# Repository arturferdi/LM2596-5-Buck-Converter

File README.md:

# LM2596-5 Fixed 5V Buck Converter

A compact step-down (buck) switching regulator based on the **Texas Instruments LM2596-5.0**, delivering a regulated **5V / 3A** output from an unregulated DC input up to 40V. Designed for embedded systems, IoT field devices, and general-purpose power supply applications.

---

## Table of Contents

- [Overview](#overview)
- [Schematic](#schematic)
- [PCB Design](#pcb-design)
- [Board Dimensions](#board-dimensions)
- [Bill of Materials (BOM)](#bill-of-materials-bom)
- [IC Electrical Characteristics](#ic-electrical-characteristics)
- [Application Design Notes](#application-design-notes)
  - [Input Capacitor (C_IN)](#input-capacitor-cin)
  - [Output Capacitor (C_OUT)](#output-capacitor-cout)
  - [Catch Diode (D1)](#catch-diode-d1)
  - [Inductor Selection](#inductor-selection)

---

## Overview

This module implements a **non-synchronous step-down DC-DC converter** using the LM2596-5.0 fixed-output variant. The LM2596 integrates all active functions for a buck regulator — including a fixed 150 kHz oscillator, internal error amplifier, and cycle-by-cycle current limiting — requiring only four external passive components.

| Parameter | Value |
|---|---|
| Topology | Non-synchronous Buck (Step-Down) |
| IC | LM2596-5.0 (TI) |
| Fixed Output Voltage | 5.0 V |
| Maximum Output Current | 3 A |
| Input Voltage Range | 7 V – 40 V |
| Switching Frequency | 150 kHz (fixed) |
| Output Voltage Accuracy | ±4% over line and load |
| Package | TO-220 (NDH) / TO-263 (KTT) |
| Thermal Protection | Yes (internal thermal shutdown) |
| Current Limit | Yes (two-stage frequency foldback) |
| Shutdown / Enable | Active-low via ON/OFF pin |

---

## Schematic

Also you can download the pdf schematic from `\PDF_Schematic`

The schematic follows the standard fixed-output buck topology per the LM2596 datasheet Figure 9-10:

---

## PCB Design

**Design rules and layout notes:**

- High-current paths (VIN → IC → L1 → VOUT and D1 freewheeling loop) use **wide copper pours** and are kept as short as possible to minimize parasitic inductance.
- The **output switch pin (Pin 1)** copper area is minimized to reduce EMI radiation from the switching node.
- C_IN and C_OUT are placed as close as possible to the IC with short return paths to GND.
- D1 (catch diode) is placed directly between Pin 2 (OUTPUT) and GND, adjacent to the IC.
- Feedback trace (Pin 4) is routed away from the inductor to prevent flux-induced noise coupling.
- **Ground plane** construction used for best noise performance.
- ON/OFF pin (Pin 5) tied to GND (regulator always enabled).
- TO-220 footprint includes heatsink pad clearance; TO-263 tab is thermally connected to a copper pour ≥ 0.4 in².

**Layer stackup:** 2-layer, 1 oz copper.

---

## Board Dimensions

| Parameter | Value |
|---|---|
| Board Size | 60 × 25 mm  |
| Mounting Holes | 2mm, 2× corner |
| Connector | Screw terminal (5.08 mm pitch), JST (2.54 mm pitch) |

---

## Bill of Materials (BOM)

| Ref | Description | Value / Part No. | Package | Qty |
|---|---|---|---|---|
| U1 | Buck Regulator IC | LM2596T-5.0/NOPB (TI) | TO-220 NDH | 1 |
| L1 | Power Inductor | 33 µH, 3.5 A | Through-hole (e.g. Renco RL-5472-4) | 1 |
| L2 | Power Inductor | 3 µH, 3.5 A | Through-hole  | 1 |
| D1 | Catch Diode | 1N5825, 5 A / 40 V Schottky | DO-201AD | 1 |
| C_IN | Input Bypass Capacitor | 470 µF / 50 V, low-ESR electrolytic | Radial | 1 |
| C_OUT | Output Filter Capacitor | 330 µF / 35 V, low-ESR electrolytic | Radial | 1 |
| C_Ripple | Ripple Filter Capacitor | 220 µF / 35 V, low-ESR electrolytic | Radial | 1 |
| J1 | Input Connector | Screw terminal, 2-pin, 5.08 mm | PCB mount | 1 |
| J2 | Input Connector | JST Connector, 2-pin, 2.54 mm | PCB mount | 1 |
| J3 | Output Connector | Screw terminal, 2-pin, 5.08 mm | PCB mount | 1 |
| J4 | Output Connector | JST Connector, 2-pin, 2.54 mm | PCB mount | 1 |

> Recommended capacitor series: **Panasonic HFQ** or **Nichicon PL** (low-ESR, switching-grade).

---

## IC Electrical Characteristics

All parameters per TI datasheet SNVS124G, T_J = 25°C unless otherwise noted.

### Absolute Maximum Ratings

| Parameter | Value | Unit |
|---|---|---|
| Maximum Supply Voltage (V_IN) | 45 | V |
| Maximum Junction Temperature | 150 | °C |
| Storage Temperature | –65 to +150 | °C |
| ESD (HBM) | ±2000 | V |

### Operating Conditions

| Parameter | Min | Max | Unit |
|---|---|---|---|
| Supply Voltage (V_IN) | 4.5 | 40 | V |
| Operating Temperature | –40 | +125 | °C |

### Electrical Characteristics — 5V Version

| Parameter | Min | Typ | Max | Unit | Conditions |
|---|---|---|---|---|---|
| Output Voltage (V_OUT) | 4.80 | 5.00 | 5.20 | V | 7 V ≤ V_IN ≤ 40 V, 0.2 A ≤ I_LOAD ≤ 3 A, T_J = 25°C |
| Output Voltage (V_OUT) | 4.75 | — | 5.25 | V | –40°C ≤ T_J ≤ 125°C |
| Output Current (I_LOAD) | — | — | 3 | A | Continuous DC |
| Efficiency (η) | — | 80 | — | % | V_IN = 12 V, I_LOAD = 3 A |
| Switching Frequency (f_O) | 127 | 150 | 173 | kHz | T_J = 25°C |
| Switching Frequency (f_O) | 110 | — | 173 | kHz | –40°C ≤ T_J ≤ 125°C |
| Peak Switch Current Limit | 3.6 | 4.5 | 6.9 | A | T_J = 25°C |
| Switch Saturation Voltage (V_SAT) | — | 1.16 | 1.40 | V | I_OUT = 3 A, T_J = 25°C |
| Standby Quiescent Current (I_STBY) | — | 80 | 200 | µA | ON/OFF = 5 V (disabled), T_J = 25°C |
| Operating Quiescent Current (I_Q) | — | 5 | 10 | mA | Switch ON |

### Thermal Information

| Package | θ_JA (typical) | θ_JC | Unit |
|---|---|---|---|
| TO-220 (NDH), no heatsink | 50 | 2 | °C/W |
| TO-263 (KTT), 0.5 in² copper | 50 | 2 | °C/W |
| TO-263 (KTT), 2.5 in² copper | 30 | 2 | °C/W |
| TO-263 (KTT), 3 in² double-sided | 20 | 2 | °C/W |

> **Note:** The TO-220 package requires an external heatsink under most operating conditions. Refer to Figure 9-18 in the LM2596 datasheet for junction temperature rise curves.

---

## Application Design Notes

### Input Capacitor (C_IN)

A **low-ESR aluminum electrolytic or solid tantalum** capacitor is mandatory between V_IN (Pin 1) and GND (Pin 3) to suppress switching transients and supply instantaneous switch-on current.

**Selection criteria:**
- **RMS current rating** ≥ 50% of DC load current (I_LOAD × 0.5). At 3 A load: I_RMS(min) = 1.5 A.
- **Voltage rating** ≥ 1.5 × V_IN(max). At 12 V input: V_rating ≥ 18 V → use 25 V or 35 V rated capacitor.
- Electrolytic capacitors must be rated for switching regulator duty (low-ESR series).

| Input Voltage (V_IN max) | Recommended Capacitor | Series |
|---|---|---|
| 10 V | 560 µF / 16 V | Panasonic HFQ / Nichicon PL |
| 15 V | 470 µF / 25 V | Panasonic HFQ / Nichicon PL |
| 25 V | 680 µF / 35 V | Panasonic HFQ / Nichicon PL |
| 40 V | 470 µF / 50 V | Panasonic HFQ / Nichicon PL |

> **Caution:** Avoid high-capacitance ceramic (MLCC) capacitors alone at V_IN — they can cause severe ringing at the input pin due to low ESR interacting with PCB inductance.

---

### Output Capacitor (C_OUT)

The output capacitor filters the inductor ripple current and directly determines output voltage ripple. **ESR is the most critical parameter.**

**Selection criteria:**
- ESR determines output ripple voltage: `V_ripple = ΔI_IND × ESR_COUT`
- Target ESR ≈ 0.1 Ω for ripple < 1% of V_OUT (50 mV pp at 5 V output).
- Capacitance range: **82 µF – 820 µF**. Do not exceed 820 µF.
- Voltage rating ≥ 1.5 × V_OUT → minimum 7.5 V. Use ≥ 25 V rated capacitor for low ESR.

| Load Current | Max V_IN | Recommended Capacitor | Inductor |
|---|---|---|---|
| 3 A | 8 V | 470 µF / 25 V | 22 µH (L41) |
| 3 A | 10 V | 560 µF / 25 V | 22 µH (L41) |
| 3 A | 15 V | 330 µF / 35 V | 33 µH (L40) |
| 3 A | 40 V | 330 µF / 35 V | 47 µH (L39) |
| 2 A | 20 V | 180 µF / 35 V | 68 µH (L38) |
| 2 A | 40 V | 180 µF / 35 V | 68 µH (L38) |

> Source: LM2596 datasheet Table 9-3 (5 V section).

> **Cold temperature note:** Below –25°C, ESR of aluminum electrolytics increases 3–10×. Use **solid tantalum capacitors** (AVX TPS or Sprague 595D series) for industrial/field deployments operating below –25°C.

---

### Catch Diode (D1)

The catch diode provides the freewheeling current path for the inductor when the internal switch is OFF. It must be **fast** and placed with minimal lead length adjacent to Pin 2 (OUTPUT) and GND.

**Selection criteria:**
- Current rating ≥ 1.3 × I_LOAD(max) → ≥ 3.9 A. Use a 5 A rated diode.
- Reverse voltage rating ≥ 1.25 × V_IN(max).
- **Schottky diodes strongly preferred** — low V_F reduces conduction loss and improves efficiency at 5 V output.
- Ultra-fast recovery types (t_rr ≤ 50 ns) are acceptable if Schottky is unavailable.
- **Do not use 1N5400-series or 1N4001-series** rectifiers — reverse recovery time is too slow for 150 kHz operation.

| V_IN (max) | Recommended Schottky | Rating |
|---|---|---|
| ≤ 20 V | 1N5823 | 5 A / 20 V |
| ≤ 30 V | 1N5824 | 5 A / 30 V |
| ≤ 40 V | **1N5825** *(default)* | 5 A / 40 V |
| ≤ 50 V | SB550 | 5 A / 50 V |

---

### Inductor Selection

The inductor is selected from TI's nomograph (Figure 9-6, LM2596-5.0) based on **maximum input voltage** and **maximum load current**, targeting continuous conduction mode (CCM).

**Inductor code reference (5 V output):**

| Inductance | Current Rating | Inductor Code | Applicable Region (5 V) |
|---|---|---|---|
| 22 µH | 3.50 A | L41 | V_IN ≤ 10 V, I_LOAD ≤ 3 A |
| 33 µH | 3.50 A | L40 | V_IN ≤ 15 V, I_LOAD ≤ 3 A |
| 47 µH | 3.50 A | L39 | V_IN ≤ 40 V, I_LOAD ≤ 3 A |
| 22 µH | 3.10 A | L33 | V_IN ≤ 9 V, I_LOAD ≤ 2 A |
| 68 µH | 3.10 A | L38 | V_IN ≤ 40 V, I_LOAD ≤ 2 A |

**Manufacturer cross-reference (33 µH / L40):**

| Manufacturer | Through-Hole P/N | Surface-Mount P/N |
|---|---|---|
| Schott | 67144220 | 67148290 |
| Renco | RL-5472-4 | — |
| Pulse Engineering | PE-54040 | PE-54040-S |

**Key formulas:**

Peak switch current:
```
I_peak = I_LOAD + (ΔI_IND / 2)
```

Minimum load for CCM:
```
I_LOAD(min, CCM) = ΔI_IND / 2
```

Output ripple voltage:
```
V_ripple = ΔI_IND × ESR_COUT
```

Required ESR for target ripple:
```
ESR_COUT = V_ripple(target) / ΔI_IND
```

> **Core type recommendation:** Use toroid or E-core (closed magnetic structure) to prevent inductor flux from coupling into the feedback trace, GND path, or output capacitor wiring. Open-core (bobbin/stick) inductors are acceptable in single-regulator designs with careful layout.

---

## License

[MIT](LICENSE) — Hardware design files and documentation are open for modification and redistribution with attribution.

---

## References

- Texas Instruments, *LM2596 SIMPLE SWITCHER® Power Converter 150-kHz 3-A Step-Down Voltage Regulator*, Datasheet SNVS124G, Rev. G, March 2023.

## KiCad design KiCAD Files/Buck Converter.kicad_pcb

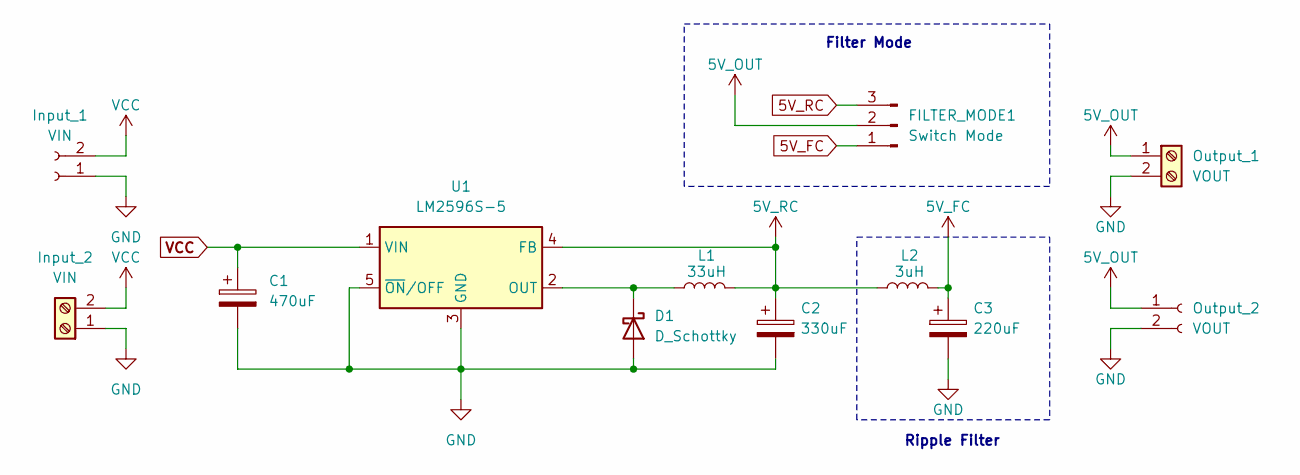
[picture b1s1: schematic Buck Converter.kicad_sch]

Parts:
C1: 470uF; CP_Radial_D5.0mm_P2.50mm
C2: 330uF; CP_Radial_D5.0mm_P2.50mm
C3: 220uF; CP_Radial_D5.0mm_P2.50mm
D1: D_Schottky; D_A-405_P10.16mm_Horizontal
FILTER_MODE1: Switch Mode; PinHeader_1x03_P2.54mm_Vertical
Input_1: VIN; JST_XH_B2B-XH-A_1x02_P2.50mm_Vertical
Input_2: VIN; TerminalBlock_RND_205-00287_1x02_P5.08mm_Horizontal
L1: 33uH; L_Toroid_Vertical_L16.0mm_W8.0mm_P7.62mm
L2: 3uH; L_Axial_L7.0mm_D3.3mm_P10.16mm_Horizontal_Fastron_MICC
Output_1: VOUT; TerminalBlock_RND_205-00287_1x02_P5.08mm_Horizontal
Output_2: VOUT; JST_XH_B2B-XH-A_1x02_P2.50mm_Vertical
U1: LM2596S-5; TO-263-5_TabPin3

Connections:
5V_FC: C3.1, FILTER_MODE1.1, L2.2
5V_OUT: FILTER_MODE1.2, Output_1.1, Output_2.1
5V_RC: C2.1, FILTER_MODE1.3, L1.2, L2.1, U1.4 (FB)
GND: C1.2, C2.2, C3.2, D1.2 (A), Input_1.1, Input_2.1, Output_1.2, Output_2.2, U1.3 (GND), U1.5 (~ON/OFF)
unnamed: D1.1 (K), L1.1, U1.2 (OUT)
VCC: C1.1, Input_1.2, Input_2.2, U1.1 (VIN)

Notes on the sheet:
Filter Mode
Ripple Filter

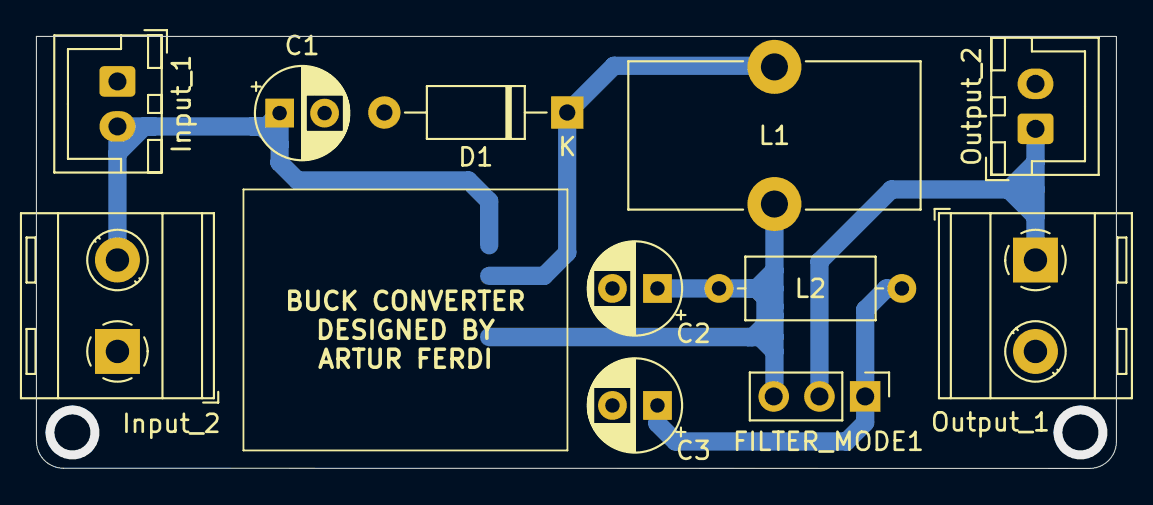
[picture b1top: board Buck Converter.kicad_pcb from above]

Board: 2 copper layers, 60.0 x 24.0 mm, 12 parts (1 on the bottom side), 6 nets.

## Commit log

2026-05-28 add files
2026-05-28 add pdf sch
2026-05-28 add additional documentation
2026-05-28 modify readme
